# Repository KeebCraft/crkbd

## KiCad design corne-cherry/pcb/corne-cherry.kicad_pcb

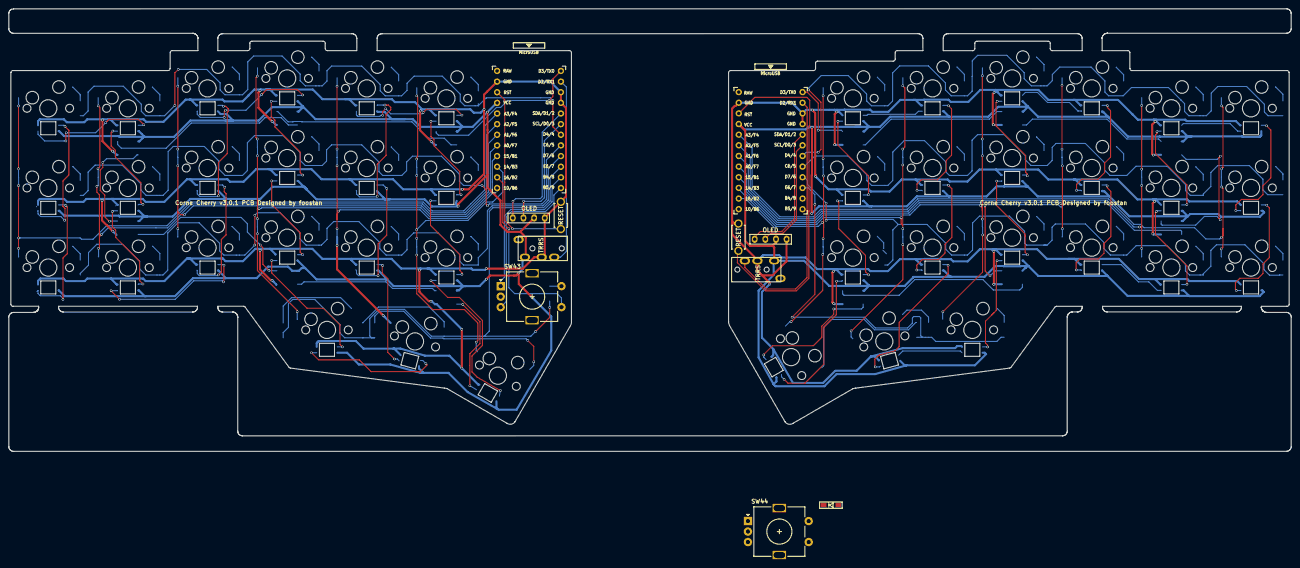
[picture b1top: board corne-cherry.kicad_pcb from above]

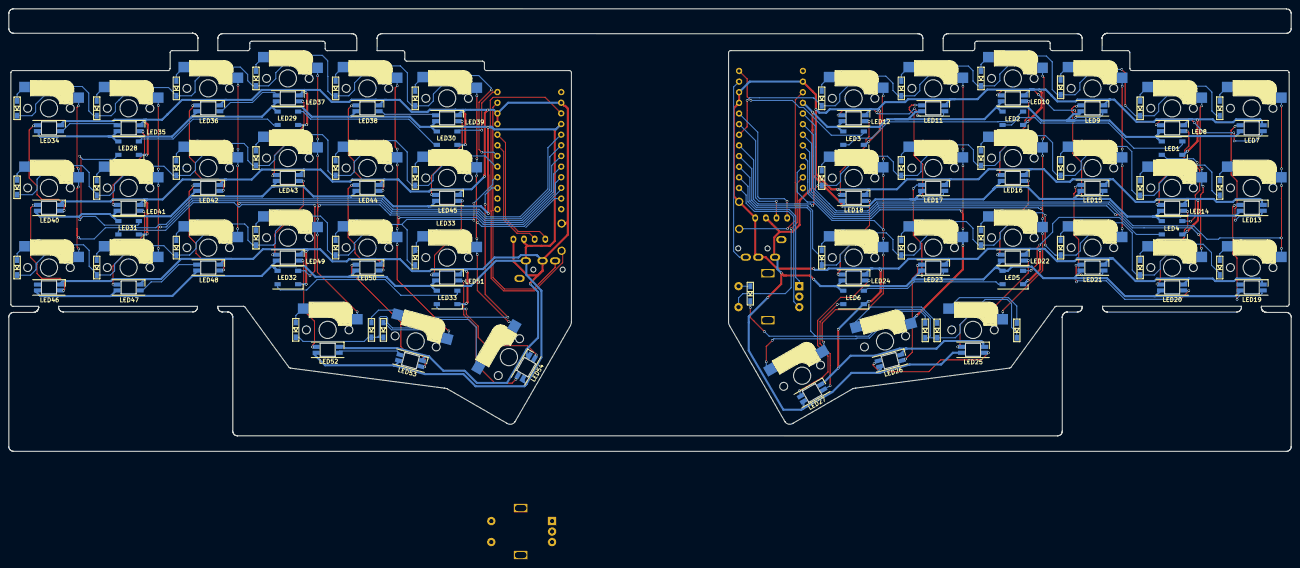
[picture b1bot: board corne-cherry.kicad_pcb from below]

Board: 2 copper layers, 306.0 x 105.6 mm, 150 parts (97 on the bottom side), 135 nets.

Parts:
D1, D2, D3, D4, D5, D6, D7, D8, D9, D10, D11, D12, D13, D14, D15, D16, D17, D18, D19, D20, D21, D22, D23, D24, D25, D26, D27, D28, D29, D30, D31, D32, D33, D34, D35, D36, D37, D38, D39, D40, D41, D42, D43, D44: D; D3_SMD_v2
J1, J3: MJ-4PP-9; MJ-4PP-9_1side
J2, J4: OLED; OLED_1side
LED1, LED2, LED3, LED4, LED5, LED6, LED28, LED29, LED30, LED31, LED32, LED33: WS2812B; LED_WS2812B_PLCC4_5.0x5.0mm_P3.2mm
LED7, LED8, LED9, LED10, LED11, LED12, LED13, LED14, LED15, LED16, LED17, LED18, LED19, LED20, LED21, LED22, LED23, LED24, LED25, LED26, LED27, LED34, LED35, LED36, LED37, LED38, LED39, LED40, LED41, LED42, LED43, LED44, LED45, LED46, LED47, LED48, LED49, LED50, LED51, LED52, LED53, LED54: YS-SK6812MINI-E
RSW1, RSW2: SW_PUSH; ResetSW_1side
SW1, SW2, SW3, SW4, SW5, SW6, SW7, SW8, SW9, SW10, SW11, SW12, SW13, SW14, SW15, SW16, SW17, SW18, SW19, SW20, SW21, SW22, SW23, SW24, SW25, SW26, SW27, SW28, SW29, SW30, SW31, SW32, SW33, SW34, SW35, SW36, SW37, SW38, SW39, SW40, SW41: SW_PUSH; CherryMX_Hotswap
SW42: SW_PUSH; CherryMX_Hotswap_1.5u
SW43, SW44: Rotary_Encoder_Switch; RotaryEncoder_Alps_EC11E-Switch_Vertical_H20mm
U1, U2: ProMicro; ProMicro_v3

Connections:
GND: J1.C, J2.4, LED1.3, LED2.3, LED3.3, LED4.3, LED5.3, LED6.3, LED7.3, LED8.3, LED9.3, LED10.3, LED11.3, LED12.3, LED13.3, LED14.3, LED15.3, LED16.3, LED17.3, LED18.3, LED19.3, LED20.3, LED21.3, LED22.3, LED23.3, LED24.3, LED25.3, LED26.3, LED27.3, RSW1.2, U1.3, U1.4, U1.23
GNDA: J3.C, J4.4, LED28.3, LED29.3, LED30.3, LED31.3, LED32.3, LED33.3, LED34.3, LED35.3, LED36.3, LED37.3, LED38.3, LED39.3, LED40.3, LED41.3, LED42.3, LED43.3, LED44.3, LED45.3, LED46.3, LED47.3, LED48.3, LED49.3, LED50.3, LED51.3, LED52.3, LED53.3, LED54.3, RSW2.2, U2.3, U2.4, U2.23
LED: LED3.4, U1.1
LED_r: LED30.4, U2.1
unnamed: D1.2, SW1.2
unnamed: D2.2, SW2.2
unnamed: D3.2, SW3.2
unnamed: D4.2, SW4.2
unnamed: D5.2, SW5.2
unnamed: D6.2, SW6.2
unnamed: D7.2, SW7.2
unnamed: D8.2, SW8.2
unnamed: D9.2, SW9.2
unnamed: D10.2, SW10.2
unnamed: D11.2, SW11.2
unnamed: D12.2, SW12.2
unnamed: D13.2, SW13.2
unnamed: D14.2, SW14.2
unnamed: D15.2, SW15.2
unnamed: D16.2, SW16.2
unnamed: D17.2, SW17.2
unnamed: D18.2, SW18.2
unnamed: D19.2, SW19.2
unnamed: D20.2, SW20.2
unnamed: D21.2, SW21.2
unnamed: D22.2, SW22.2
unnamed: D23.2, SW23.2
unnamed: D24.2, SW24.2
unnamed: D25.2, SW25.2
unnamed: D26.2, SW26.2
unnamed: D27.2, SW27.2
unnamed: D28.2, SW28.2
unnamed: D29.2, SW29.2
unnamed: D30.2, SW30.2
unnamed: D31.2, SW31.2
unnamed: D32.2, SW32.2
unnamed: D33.2, SW33.2
unnamed: D34.2, SW34.2
unnamed: D35.2, SW35.2
unnamed: D36.2, SW36.2
unnamed: D37.2, SW37.2
unnamed: D38.2, SW38.2
unnamed: D39.2, SW39.2
unnamed: D40.2, SW40.2
unnamed: D41.2, SW41.2
unnamed: D42.2, SW42.2
unnamed: D43.2, SW43.S2
unnamed: D44.2, SW44.S2
unnamed: LED1.2, LED4.4
unnamed: LED1.4, LED2.2
unnamed: LED2.4, LED3.2
unnamed: LED4.2, LED5.4
unnamed: LED5.2, LED6.4
unnamed: LED7.4, LED8.2
unnamed: LED9.4, LED10.2
unnamed: LED10.4, LED16.2
unnamed: LED11.2, LED17.4
unnamed: LED11.4, LED12.2
unnamed: LED12.4, LED18.2
unnamed: LED13.2, LED19.4
unnamed: LED7.2, LED13.4
unnamed: LED8.4, LED14.2
unnamed: LED14.4, LED20.2
unnamed: LED15.2, LED21.4
unnamed: LED9.2, LED15.4
unnamed: LED16.4, LED22.2
unnamed: LED17.2, LED23.4
unnamed: LED18.4, LED24.2
unnamed: LED20.4, LED21.2
unnamed: LED22.4, LED25.2
unnamed: LED23.2, LED26.4
unnamed: LED24.4, LED27.2
unnamed: LED25.4, LED26.2
unnamed: LED6.2, LED27.4
unnamed: LED28.2, LED31.4
unnamed: LED28.4, LED29.2
unnamed: LED29.4, LED30.2
unnamed: LED31.2, LED32.4
unnamed: LED32.2, LED33.4
unnamed: LED33.2, LED54.4
unnamed: LED34.2, LED40.4
unnamed: LED34.4, LED35.2
unnamed: LED35.4, LED41.2
unnamed: LED36.2, LED42.4
unnamed: LED36.4, LED37.2
unnamed: LED37.4, LED43.2
unnamed: LED38.2, LED44.4
unnamed: LED38.4, LED39.2
unnamed: LED39.4, LED45.2
unnamed: LED40.2, LED46.4
unnamed: LED41.4, LED47.2
unnamed: LED42.2, LED48.4
unnamed: LED43.4, LED49.2
unnamed: LED44.2, LED50.4
unnamed: LED45.4, LED51.2
unnamed: LED47.4, LED48.2
unnamed: LED49.4, LED52.2
unnamed: LED50.2, LED53.4
unnamed: LED51.4, LED54.2
unnamed: LED52.4, LED53.2
SCL: J2.2, U1.6
SCL_r: J4.2, U2.6
SDA: J2.1, U1.5
SDA_r: J4.1, U2.5
VCC: J1.D, J2.3, LED1.1, LED2.1, LED3.1, LED4.1, LED5.1, LED6.1, LED7.1, LED8.1, LED9.1, LED10.1, LED11.1, LED12.1, LED13.1, LED14.1, LED15.1, LED16.1, LED17.1, LED18.1, LED19.1, LED20.1, LED21.1, LED22.1, LED23.1, LED24.1, LED25.1, LED26.1, LED27.1, U1.21
VDD: J3.D, J4.3, LED28.1, LED29.1, LED30.1, LED31.1, LED32.1, LED33.1, LED34.1, LED35.1, LED36.1, LED37.1, LED38.1, LED39.1, LED40.1, LED41.1, LED42.1, LED43.1, LED44.1, LED45.1, LED46.1, LED47.1, LED48.1, LED49.1, LED50.1, LED51.1, LED52.1, LED53.1, LED54.1, U2.21
col0: SW1.1, SW7.1, SW13.1, U1.20
col0_r: SW22.1, SW28.1, SW34.1, U2.20
col1: SW2.1, SW8.1, SW14.1, U1.19
col1_r: SW23.1, SW29.1, SW35.1, U2.19
col2: SW3.1, SW9.1, SW15.1, U1.18
col2_r: SW24.1, SW30.1, SW36.1, U2.18
col3: SW4.1, SW10.1, SW16.1, SW19.1, U1.17
col3_r: SW25.1, SW31.1, SW37.1, SW40.1, U2.17
col4: SW5.1, SW11.1, SW17.1, SW20.1, U1.16
col4_r: SW26.1, SW32.1, SW38.1, SW41.1, U2.16
col5: SW6.1, SW12.1, SW18.1, SW21.1, U1.15
col5_r: SW27.1, SW33.1, SW39.1, SW42.1, U2.15
col6: SW43.S1, U1.14
col6_r: SW44.S1, U2.14
data: J1.B, U1.2
data_r: J3.B, U2.2
enca: SW43.A, U1.11
enca_r: SW44.A, SW44.B, U2.11
encb: SW43.B, U1.12
reset: RSW1.1, U1.22
reset_r: RSW2.1, U2.22
row0: D1.1, D2.1, D3.1, D4.1, D5.1, D6.1, U1.7
row0_r: D22.1, D23.1, D24.1, D25.1, D26.1, D27.1, U2.7
row1: D7.1, D8.1, D9.1, D10.1, D11.1, D12.1, U1.8
row1_r: D28.1, D29.1, D30.1, D31.1, D32.1, D33.1, U2.8
row2: D13.1, D14.1, D15.1, D16.1, D17.1, D18.1, U1.9
row2_r: D34.1, D35.1, D36.1, D37.1, D38.1, D39.1, U2.9
row3: D19.1, D20.1, D21.1, D43.1, U1.10
row3_r: D40.1, D41.1, D42.1, D44.1, U2.10

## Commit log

2021-02-22 Added encoder to left half of Corne. Moved MCU, reset, and TRRS up and reduced 1.5u thumb key to 1u to accomodate.
